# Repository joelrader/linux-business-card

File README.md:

# linux-business-card
A business card that runs Linux!

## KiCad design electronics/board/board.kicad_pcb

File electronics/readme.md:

# Electrical Design
The main AP is an Allwinner F1C100s.

## Power Rails

VCC-IO: 3.3V @ ?A
TV_AVCC: 3.3V @ ?A
Avcc: 2.8V @ ?A
VCC_DRAM: 2.5V @ ?A
VDD_CORE: 1.1V @ ?A

## Components
SMPS
    - JW5211
        - Looks decent

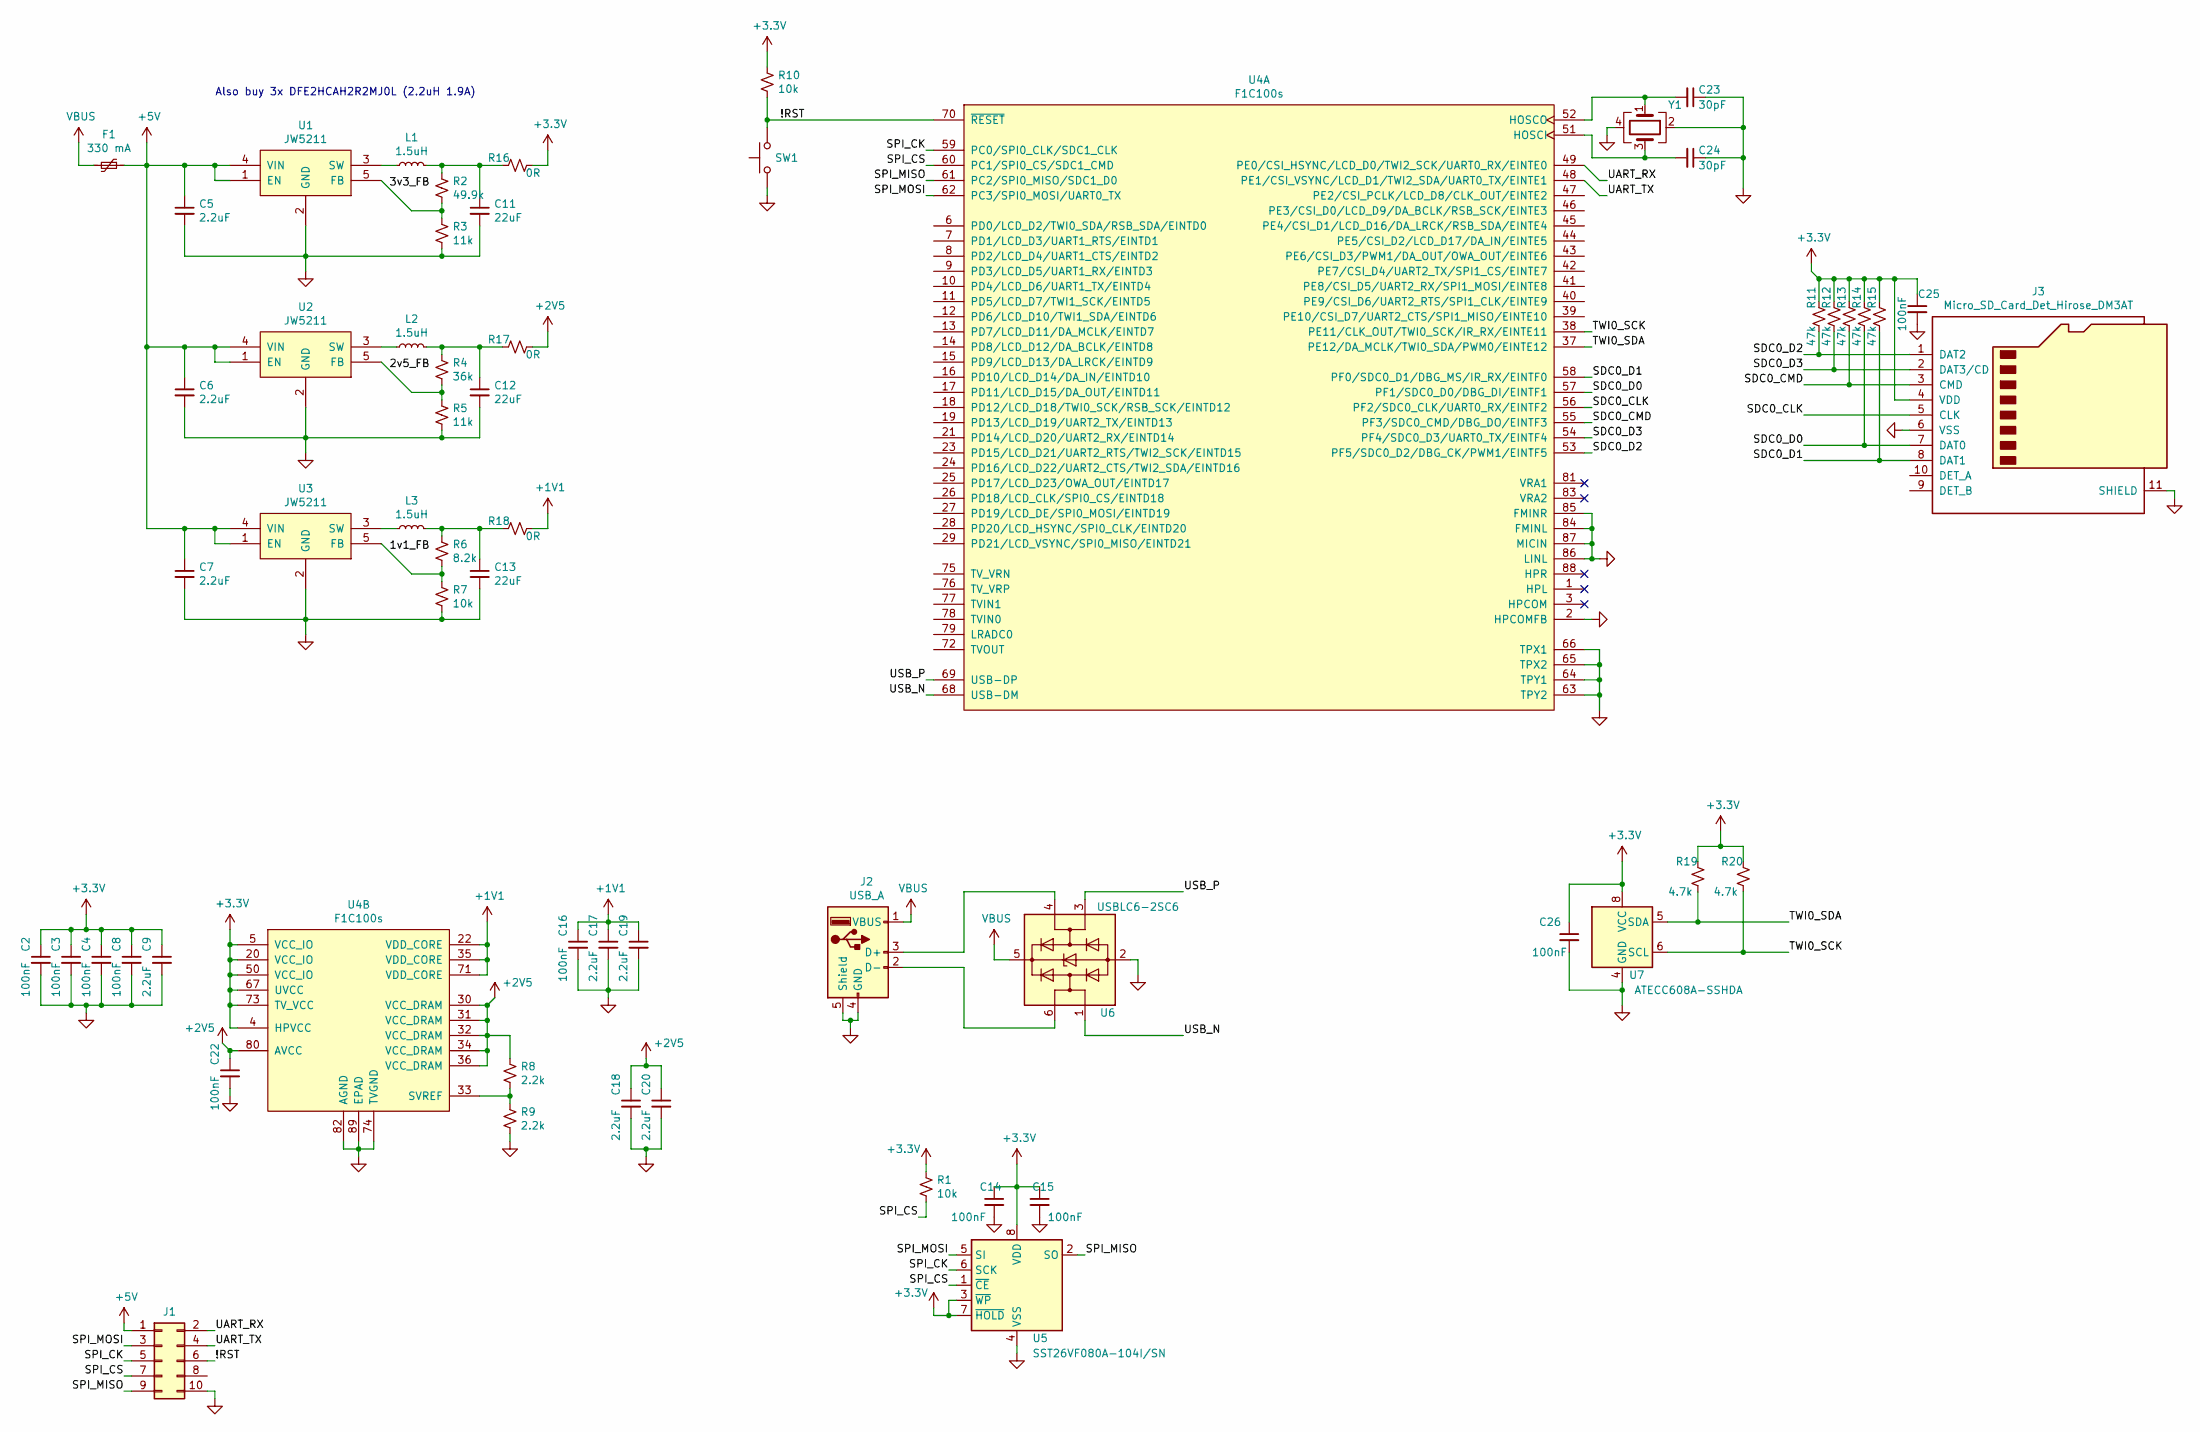
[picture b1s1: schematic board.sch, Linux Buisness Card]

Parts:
C2, C3, C4, C8, C14, C15, C16, C22, C25, C26: 100nF; C_0603_1608Metric
C5, C6, C7, C9, C17, C18, C19, C20: 2.2uF; C_0603_1608Metric
C11, C12, C13: 22uF; C_0805_2012Metric
C23, C24: 30pF; C_0603_1608Metric
F1: 330 mA; Fuse_0603_1608Metric; MPN PRG18BC4R7MM1RB
J1: Conn_02x05_Odd_Even; PinSocket_2x05_P2.54mm_Vertical
J2: USB_A; USB_A_CNCTech_1001-011-01101_Horizontal; MPN 1001-011-01101
J3: Micro_SD_Card_Det_Hirose_DM3AT; microSD_HC_Hirose_DM3AT-SF-PEJM5
L1, L2, L3: 1.5uH; L_1008_2520Metric; MPN CVH252009-1R5M
R1, R7, R10: 10k; R_0603_1608Metric
R2: 49.9k; R_0603_1608Metric
R3, R5: 11k; R_0603_1608Metric
R4: 36k; R_0603_1608Metric
R6: 8.2k; R_0603_1608Metric
R8, R9: 2.2k; R_0603_1608Metric
R11, R12, R13, R14, R15: 47k; R_0603_1608Metric
R16, R17, R18: 0R; R_0603_1608Metric
R19, R20: 4.7k; R_0603_1608Metric
SW1: SW_Push; SW_SPST_TL3342
U1, U2, U3: JW5211; SOT-23-5
U4: F1C100s; QFN-88_EP_10x10_Pitch0.4mm
U5: SST26VF080A-104I/SN; SOIC-8_5.275x5.275mm_P1.27mm; MPN SST26VF080A-104I/SN
U6: USBLC6-2SC6; SOT-23-6
U7: ATECC608A-SSHDA; SOIC-8_3.9x4.9mm_P1.27mm
Y1: Crystal_GND24; Crystal_SMD_Abracon_ABM8G-4Pin_3.2x2.5mm; MPN ABM8G-24.000MHZ-18-D2Y-T

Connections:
+1V1: C16.1, C17.1, C19.1, R18.1, U4.22 (VDD_CORE), U4.35 (VDD_CORE), U4.71 (VDD_CORE)
+2V5: C18.1, C20.1, C22.1, R8.1, R17.1, U4.30 (VCC_DRAM), U4.31 (VCC_DRAM), U4.32 (VCC_DRAM), U4.34 (VCC_DRAM), U4.36 (VCC_DRAM), U4.80 (AVCC)
+3V3: C2.1, C3.1, C4.1, C8.1, C9.1, C14.1, C15.1, C25.1, C26.1, J3.4 (VDD), R1.1, R10.1, R11.1, R12.1, R13.1, R14.1, R15.1, R16.1, R19.1, R20.1, U4.4 (HPVCC), U4.5 (VCC_IO), U4.20 (VCC_IO), U4.50 (VCC_IO), U4.67 (UVCC), U4.73 (TV_VCC), U5.3 (~WP~), U5.7 (~HOLD~), U5.8 (VDD), U7.8 (VCC)
+5V: C5.1, C6.1, C7.1, F1.1, J1.1, U1.1 (EN), U1.4 (VIN), U2.1 (EN), U2.4 (VIN), U3.1 (EN), U3.4 (VIN)
/1v1_FB: R6.2, R7.1, U3.5 (FB)
/2v5_FB: R4.2, R5.1, U2.5 (FB)
/3v3_FB: R2.2, R3.1, U1.5 (FB)
/!RST: J1.6, R10.2, SW1.2, U4.70 (~RESET)
/SDC0_CLK: J3.5 (CLK), U4.56 (PF2/SDC0_CLK/UART0_RX/EINTF2)
/SDC0_CMD: J3.3 (CMD), R13.2, U4.55 (PF3/SDC0_CMD/DBG_DO/EINTF3)
/SDC0_D0: J3.7 (DAT0), R14.2, U4.57 (PF1/SDC0_D0/DBG_DI/EINTF1)
/SDC0_D1: J3.8 (DAT1), R15.2, U4.58 (PF0/SDC0_D1/DBG_MS/IR_RX/EINTF0)
/SDC0_D2: J3.1 (DAT2), R11.2, U4.53 (PF5/SDC0_D2/DBG_CK/PWM1/EINTF5)
/SDC0_D3: J3.2 (DAT3/CD), R12.2, U4.54 (PF4/SDC0_D3/UART0_TX/EINTF4)
/SPI_CK: J1.5, U4.59 (PC0/SPI0_CLK/SDC1_CLK), U5.6 (SCK)
/SPI_CS: J1.7, R1.2, U4.60 (PC1/SPI0_CS/SDC1_CMD), U5.1 (~CE)
/SPI_MISO: J1.9, U4.61 (PC2/SPI0_MISO/SDC1_D0), U5.2 (SO)
/SPI_MOSI: J1.3, U4.62 (PC3/SPI0_MOSI/UART0_TX), U5.5 (SI)
/TWI0_SCK: R20.2, U4.38 (PE11/CLK_OUT/TWI0_SCK/IR_RX/EINTE11), U7.6 (SCL)
/TWI0_SDA: R19.2, U4.37 (PE12/DA_MCLK/TWI0_SDA/PWM0/EINTE12), U7.5 (SDA)
/UART_RX: J1.2, U4.49 (PE0/CSI_HSYNC/LCD_D0/TWI2_SCK/UART0_RX/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)
/UART_TX: J1.4, U4.48 (PE1/CSI_VSYNC/LCD_D1/TWI2_SDA/UART0_TX/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)
/USB_N: U4.68 (USB-DM), U6.1 (I/O1)
/USB_P: U4.69 (USB-DP), U6.3 (I/O2)
GND: C2.2, C3.2, C4.2, C5.2, C6.2, C7.2, C8.2, C9.2, C11.2, C12.2, C13.2, C14.2, C15.2, C16.2, C17.2, C18.2, C19.2, C20.2, C22.2, C23.1, C24.1, C25.2, C26.2, J1.10, J2.4 (GND), J2.5 (Shield), J3.6 (VSS), J3.11 (SHIELD), R3.2, R5.2, R7.2, R9.2, SW1.1, U1.2 (GND), U2.2 (GND), U3.2 (GND), U4.2 (HPCOMFB), U4.63 (TPY2), U4.64 (TPY1), U4.65 (TPX2), U4.66 (TPX1), U4.74 (TVGND), U4.82 (AGND), U4.84 (FMINL), U4.85 (FMINR), U4.86 (LINL), U4.87 (MICIN), U4.89 (EPAD), U5.4 (VSS), U6.2 (GND), U7.4 (GND), Y1.2, Y1.4; also elsewhere on the board
unnamed: C11.1, L1.2, R2.1, R16.2
unnamed: C12.1, L2.2, R4.1, R17.2
unnamed: C13.1, L3.2, R6.1, R18.2
unnamed: C23.2, U4.52 (HOSCO), Y1.1
unnamed: C24.2, U4.51 (HOSCI), Y1.3
unnamed: J2.2 (D-), U6.6 (I/O1)
unnamed: J2.3 (D+), U6.4 (I/O2)
unnamed: L1.1, U1.3 (SW)
unnamed: L2.1, U2.3 (SW)
unnamed: L3.1, U3.3 (SW)
unnamed: R8.2, R9.1, U4.33 (SVREF)
unnamed 40: U4.14 (PD8/LCD_D12/DA_BCLK/EINTD8); also elsewhere on the board
VBUS: F1.2, J2.1 (VBUS), U6.5 (VBUS)

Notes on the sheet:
Also buy 3x DFE2HCAH2R2MJ0L (2.2uH 1.9A)

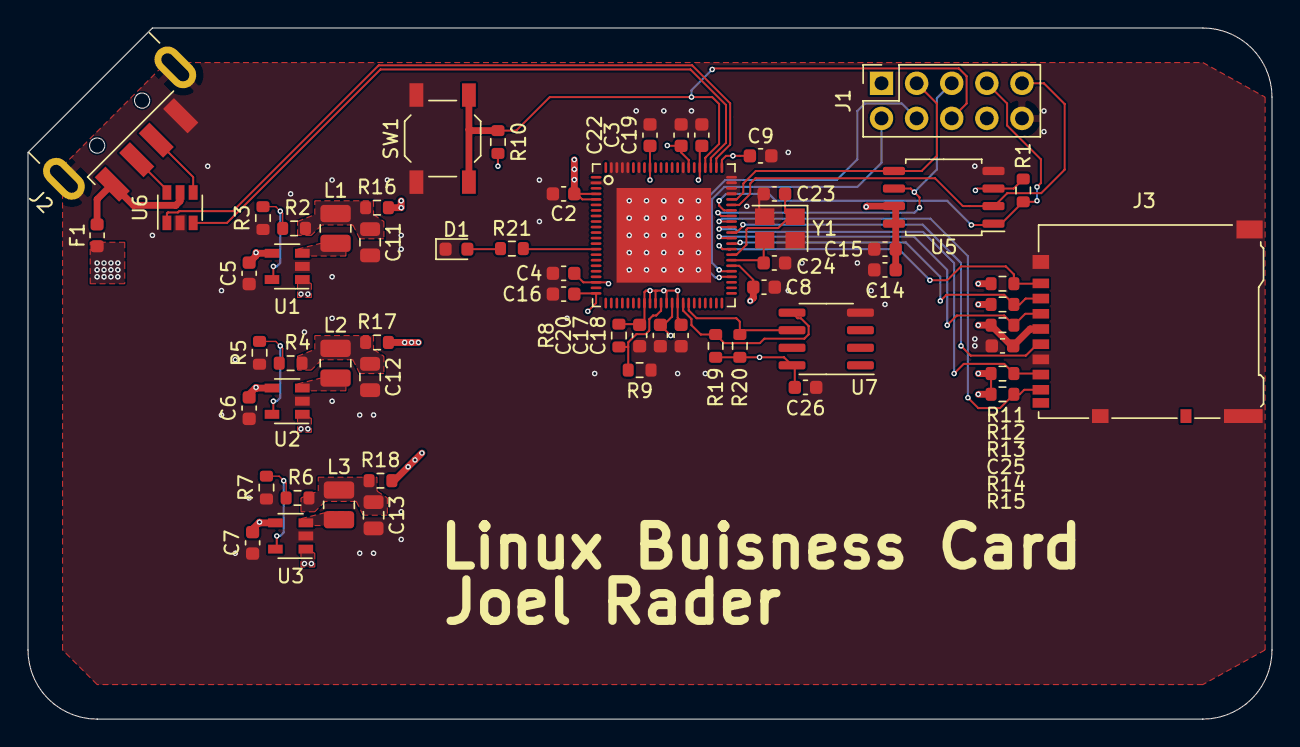
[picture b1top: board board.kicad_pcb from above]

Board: 4 copper layers, 90.0 x 50.0 mm, 61 parts (0 on the bottom side), 39 nets.

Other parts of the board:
D1: LED; LED_0603_1608Metric
R21: 4.7k; R_0603_1608Metric

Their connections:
GND: D1.1; also elsewhere on the board
unnamed: D1.2, R21.2
unnamed 40: R21.1; also elsewhere on the board

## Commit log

2021-06-29 Initial commit, AP dropped in, added some datasheets.
2021-07-02 Added some components and studied some datasheets.
2021-07-02 Dropped in the power supplies and hooked up the AP.
2021-07-05 Flash in, header in, UART in, Crystal in. Wired up most of the board.
2021-07-14 Added user manual, dropped in SD card holder into schematic.
2021-07-14 Selected inductors.
2021-07-14 Added USB power protection, started adding package footprints.
2021-07-14 Added ATECC608B security chip and filled in the rest of footprints.
2021-07-14 Removed unused USB lib
2021-07-14 Dropped all the part on the board.
2021-07-21 Arranged the parts.
2021-07-21 Dropped in the 3d models and outlined the board.
2021-07-23 Started the main routing.
2021-07-23 Nearly finished up all the layout, power distrobution done. Just a couple more nets to connect up and silk.
2021-07-27 Layout finished, added some images.
2021-07-27 Formatting
2021-07-27 Added some notes.
2021-07-27 typo
2021-07-27 Filled in the rest of the part numbers, generated a bom.
